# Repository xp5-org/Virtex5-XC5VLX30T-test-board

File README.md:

# 4 layer test-board for the XC5VLX30T-1FF665I-ND
schematic & pcb designed in Kicad 8
>This is a work in progress, i will update again after completing the bga reball work and confirming if the chips respond to jtag
>- capcaitor footprints not finalized (may need more depending on what testing reveals)
<br><br>

This project's goal is to fan out as many I/O pins as possible on the Virtex-5 665 BGA , 1mm pitch footprint, using a standard PCB service without any special work. This means:
- 0.3 drill size vias
- 0.15mm track spacing & track width
- 0.2mm copper-to-hole clearance
- 4 layers, 1oz
- NO microvia, blind via, buried via
- NO via-in-pad

With these constraints, I was able to pull 215 I/O pins on a standard 4-layer board.  
Warning: This design is on the extreme edge of "not following the manufacturers PCB design recommendations" with regards to the signal and power delivery
I'm not certain if this will work for any practical design (VGA, Ethernet, DDR-SDRAM). However it should be acceptable for hobby work and experimenting.
I initially planned to interface this Virtex-5 FPGA with some 3.3v cmos buffers and logic gates, high-speed wasn't a concern.
If the scrap-recovered chips i have respond & work, this design could be easily converted to a 6-layer to improve power plane & signal
<br><br>

# pcb ordering & build
For this 4-layer version, i had [PCBWay](https://www.pcbway.com/) build it and i put together a youtube video of what it looks like
- Current pcbway board - https://www.youtube.com/watch?v=_ErQVJeHTFE , here I am showing some close up photos reviewing what was built and received. In this video i can confirm what pcbway's capabilities are on standard pcb service, specifically in this board design there is some critical areas around hole drill precision & plating for the vias. the precision by pcbway will allow to use 0.15mm copper clearance in this design and can see in this video link.
- PCBWay by default offered 1oz copper on inner & outer layers, which gave more current carrying capability for VCCINT and VCCO
- order sheet for PCBWay - https://github.com/xp5-org/Virtex5-XC5VLX30T-test-board/blob/main/pcbway_4layer_order.png , this is using default options for 4-layer with the exception of trace width & spacing has been specified to 5mil

<br><br>

# Current Status
- this is the basic idea of what i'm working with. a Xilinx programmer is $30+ and a raspi with [XC3SPROG](https://xc3sprog.sourceforge.net/hardware.php) is $5
- the raspi will have to live on this device and use the jtag header to program the virtex5 on each use or powerup.
- There is a lot of I/O, but there's nothing else. no ram, no EPROM, no flash.

<br><br>

Power:  The virtex5 here needs 1.0V, 2.5V, and 3.3V
- I'm starting off with the MP2307 buck converter, its an inexpensive (and discontinued) chip found in the mini360 modules
- SMD version : https://github.com/xp5-org/Virtex5-XC5VLX30T-test-board/tree/main/XC5VLX30T_testboard/buck_converter_mp2307
- Through-hole version: https://github.com/xp5-org/Virtex5-XC5VLX30T-test-board/tree/main/XC5VLX30T_testboard/mp2307_tht

<br><br>

Next steps for testing:
- build the MP2307 buck converters
- reball the virtex5's using 0.6mm lead balls
 
<br><br><br><br>
# kicad screenshots of each layer
<br><br>

JTAG pins on the rear, clock and capacitors on the bottom GND plane side
headers for buck converters at the top of the board

Top Layer:

2nd Layer:

3rd Layer:

4th Layer:

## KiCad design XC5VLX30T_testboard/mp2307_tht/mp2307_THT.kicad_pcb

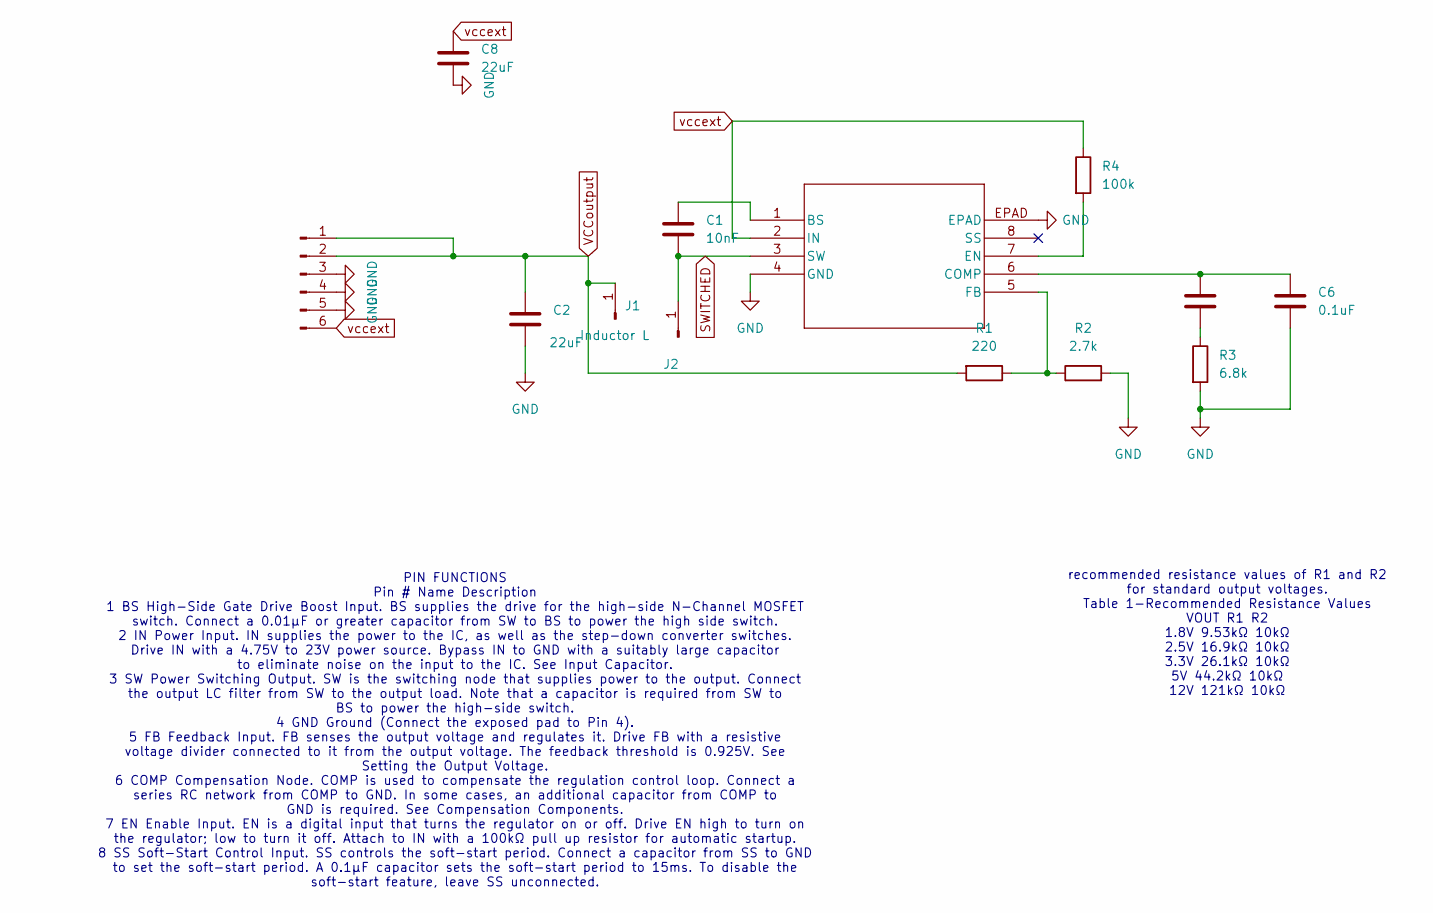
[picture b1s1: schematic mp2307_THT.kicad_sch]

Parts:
C1: 10nF; C_Disc_D3.0mm_W1.6mm_P2.50mm
C2, C8: 22uF; C_Disc_D3.0mm_W1.6mm_P2.50mm
C3: 3.9nF; C_Disc_D3.0mm_W1.6mm_P2.50mm
C6: 0.1uF; C_Disc_D3.0mm_W1.6mm_P2.50mm
J1: Inductor L; PinHeader_1x01_P2.54mm_Vertical
J2: Inductor_R; PinHeader_1x01_P2.54mm_Vertical
J4: Conn_01x06_Pin; virtex5_buck
R1: 220; R_Axial_DIN0204_L3.6mm_D1.6mm_P1.90mm_Vertical
R2: 2.7k; R_Axial_DIN0204_L3.6mm_D1.6mm_P1.90mm_Vertical
R3: 6.8k; R_Axial_DIN0204_L3.6mm_D1.6mm_P1.90mm_Vertical
R4: 100k; R_Axial_DIN0204_L3.6mm_D1.6mm_P1.90mm_Vertical
U1: MP2307DN-LF-Z; IC8_MP2307_MNP

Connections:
GND: C2.2, C6.2, C8.2, J4.3, J4.4, J4.5, R2.2, R3.2, U1.4 (GND), U1.EPAD
unnamed: C3.2, R3.1
unnamed: C1.1, U1.1 (BS)
unnamed: C3.1, C6.1, U1.6 (COMP)
unnamed: R4.2, U1.7 (EN)
unnamed: R1.1, R2.1, U1.5 (FB)
SWITCHED: C1.2, J2.1, U1.3 (SW)
VCCoutput: C2.1, J1.1, J4.1, J4.2, R1.2
vccext: C8.1, J4.6, R4.1, U1.2 (IN)

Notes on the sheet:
recommended resistance values of R1 and R2 for standard output voltages. Table 1-Recommended Resistance Values VOUT R1 R2 1.8V 9.53kΩ 10kΩ 2.5V 16.9kΩ 10kΩ 3.3V 26.1kΩ 10kΩ 5V 44.2kΩ 10kΩ 12V 121kΩ 10kΩ
PIN FUNCTIONS Pin # Name Description 1 BS High-Side Gate Drive Boost Input. BS supplies the drive for the high-side N-Channel MOSFET switch. Connect a 0.01μF or greater capacitor from SW to BS to power the high side switch. 2 IN Power Input. IN supplies the power to the IC, as well as the step-down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

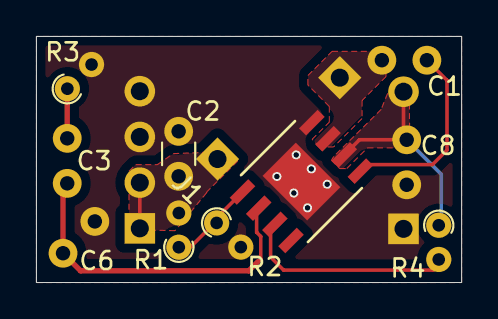
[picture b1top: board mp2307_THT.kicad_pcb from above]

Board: 2 copper layers, 23.6 x 13.7 mm, 13 parts (0 on the bottom side), 9 nets.

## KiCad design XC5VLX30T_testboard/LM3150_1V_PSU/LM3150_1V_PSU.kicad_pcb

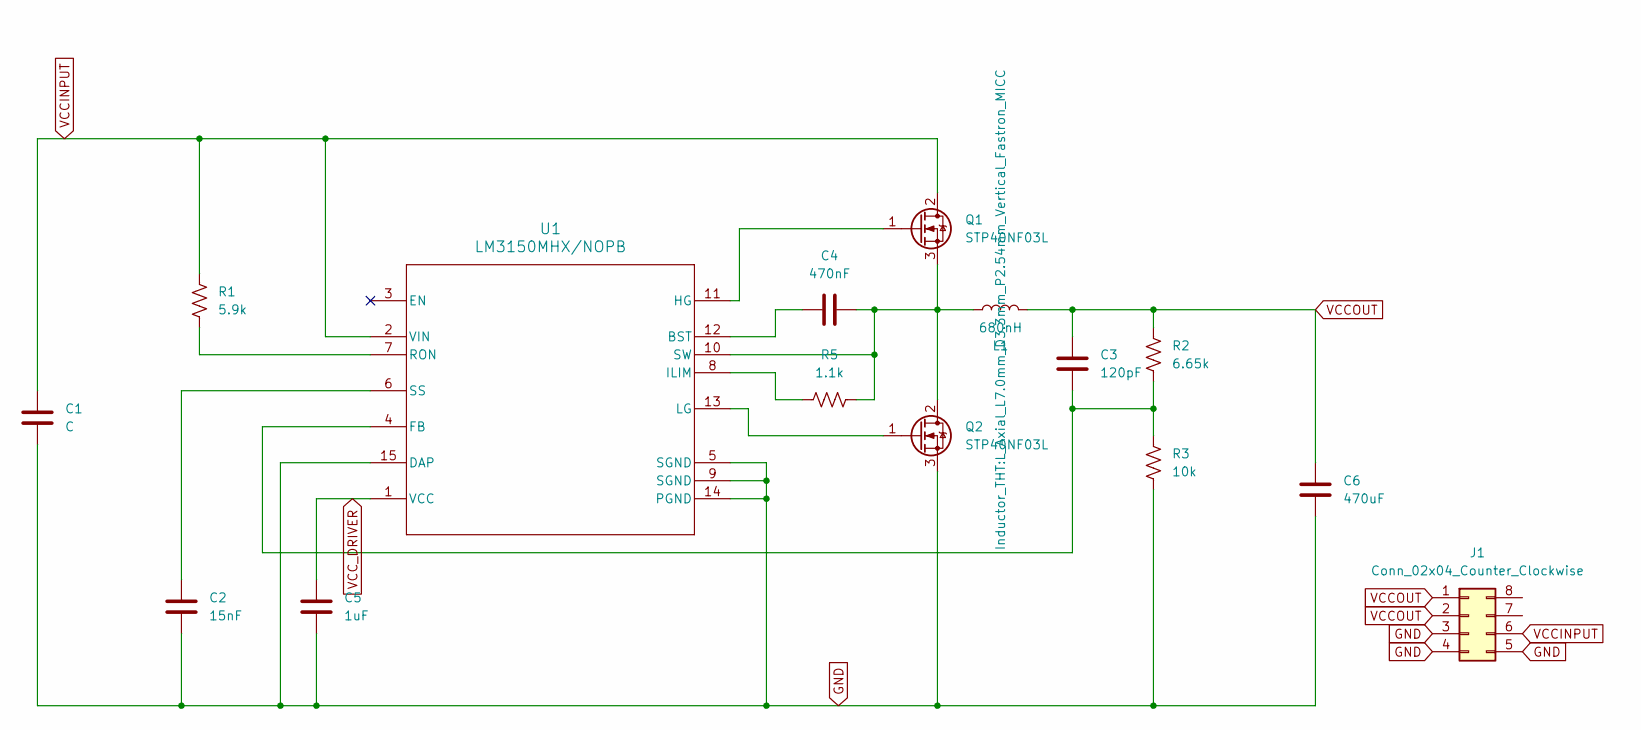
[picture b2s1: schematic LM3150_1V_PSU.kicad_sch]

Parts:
C1: C; C_Disc_D3.0mm_W2.0mm_P2.50mm
C2: 15nF; C_Disc_D3.0mm_W1.6mm_P2.50mm
C3: 120pF; C_Disc_D3.0mm_W1.6mm_P2.50mm
C4: 470nF; C_Disc_D3.0mm_W1.6mm_P2.50mm
C5: 1uF; C_Disc_D3.0mm_W1.6mm_P2.50mm
C6: 470uF; C_Disc_D3.0mm_W1.6mm_P2.50mm
J1: Conn_02x04_Counter_Clockwise; virtex5_buck
L1: 680nH; L_Axial_L7.0mm_D3.3mm_P2.54mm_Vertical_Fastron_MICC
Q1, Q2: STP40NF03L; TO-220-3_Vertical
R1: 5.9k; R_Axial_DIN0204_L3.6mm_D1.6mm_P5.08mm_Horizontal
R2: 6.65k; R_Axial_DIN0204_L3.6mm_D1.6mm_P5.08mm_Horizontal
R3: 10k; R_Axial_DIN0204_L3.6mm_D1.6mm_P5.08mm_Horizontal
R5: 1.1k; R_Axial_DIN0204_L3.6mm_D1.6mm_P5.08mm_Horizontal
U1: LM3150MHX/NOPB; HTSSOP-14-1EP_4.4x5mm_P0.65mm_EP3.4x5mm_Mask3x3.1mm_Thermal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

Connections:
GND: C1.2, C2.2, C5.2, C6.2, J1.3, J1.4, J1.5, Q2.3 (S), R3.2, U1.5 (SGND), U1.9 (SGND), U1.14 (PGND), U1.15 (DAP)
unnamed: Q1.1 (G), U1.11 (HG)
unnamed: C4.1, L1.2, Q1.3 (S), Q2.2 (D), R5.1, U1.10 (SW)
unnamed: Q2.1 (G), U1.13 (LG)
unnamed: C4.2, U1.12 (BST)
unnamed: C3.2, R2.2, R3.1, U1.4 (FB)
unnamed: R5.2, U1.8 (ILIM)
unnamed: R1.2, U1.7 (RON)
unnamed: C2.1, U1.6 (SS)
VCCINPUT: C1.1, J1.6, Q1.2 (D), R1.1, U1.2 (VIN)
VCCOUT: C3.1, C6.1, J1.1, J1.2, L1.1, R2.1
VCC_DRIVER: C5.1, U1.1 (VCC)

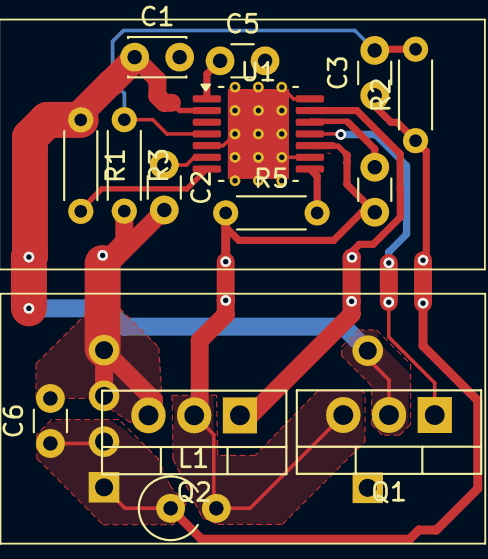
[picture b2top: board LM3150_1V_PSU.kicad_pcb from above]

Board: 2 copper layers, 15 parts (0 on the bottom side), 12 nets.

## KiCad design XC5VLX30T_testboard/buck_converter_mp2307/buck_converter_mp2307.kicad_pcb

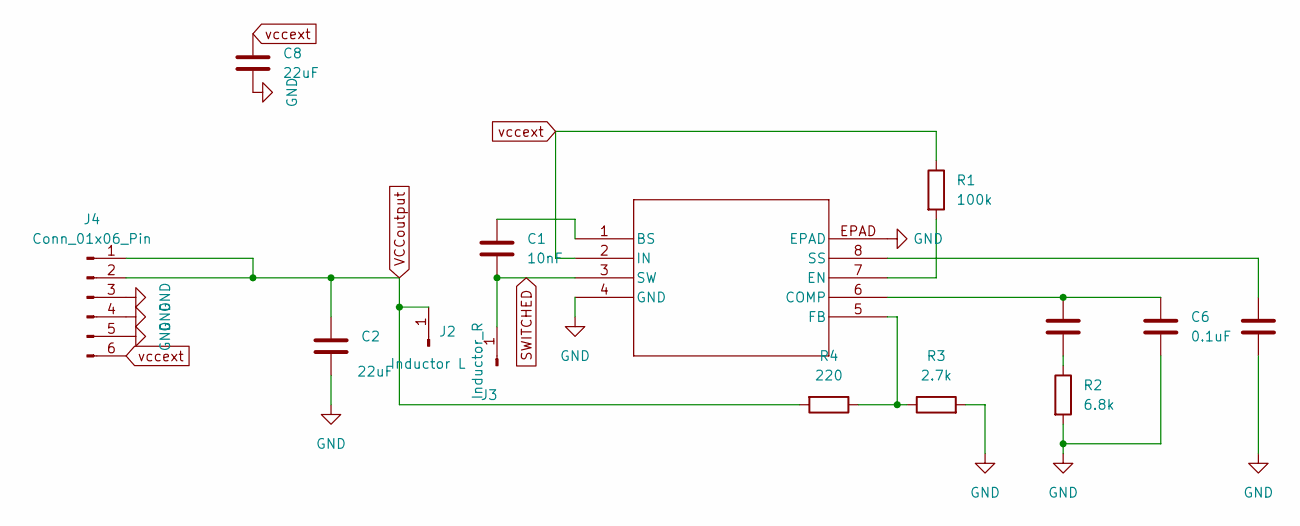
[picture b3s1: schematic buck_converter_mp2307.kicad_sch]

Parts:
C1: 10nF; C_0603_1608Metric
C2, C8: 22uF; C_1206_3216Metric
C3: 3.9nF; C_0603_1608Metric
C4, C6: 0.1uF; C_0603_1608Metric
J2: Inductor L; PinHeader_1x01_P2.54mm_Vertical
J3: Inductor_R; PinHeader_1x01_P2.54mm_Vertical
J4: Conn_01x06_Pin; virtex5_buck
R1: 100k; R_0603_1608Metric
R2: 6.8k; R_0603_1608Metric
R3: 2.7k; R_0603_1608Metric
R4: 220; R_0603_1608Metric
U1: MP2307DN-LF-Z; IC8_MP2307_MNP

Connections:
GND: C2.2, C4.2, C6.2, C8.2, J4.3, J4.4, J4.5, R2.2, R3.2, U1.4 (GND), U1.EPAD
unnamed: C3.2, R2.1
unnamed: C1.1, U1.1 (BS)
unnamed: C3.1, C6.1, U1.6 (COMP)
unnamed: R1.2, U1.7 (EN)
unnamed: R3.1, R4.1, U1.5 (FB)
unnamed: C4.1, U1.8 (SS)
SWITCHED: C1.2, J3.1, U1.3 (SW)
VCCoutput: C2.1, J2.1, J4.1, J4.2, R4.2
vccext: C8.1, J4.6, R1.1, U1.2 (IN)

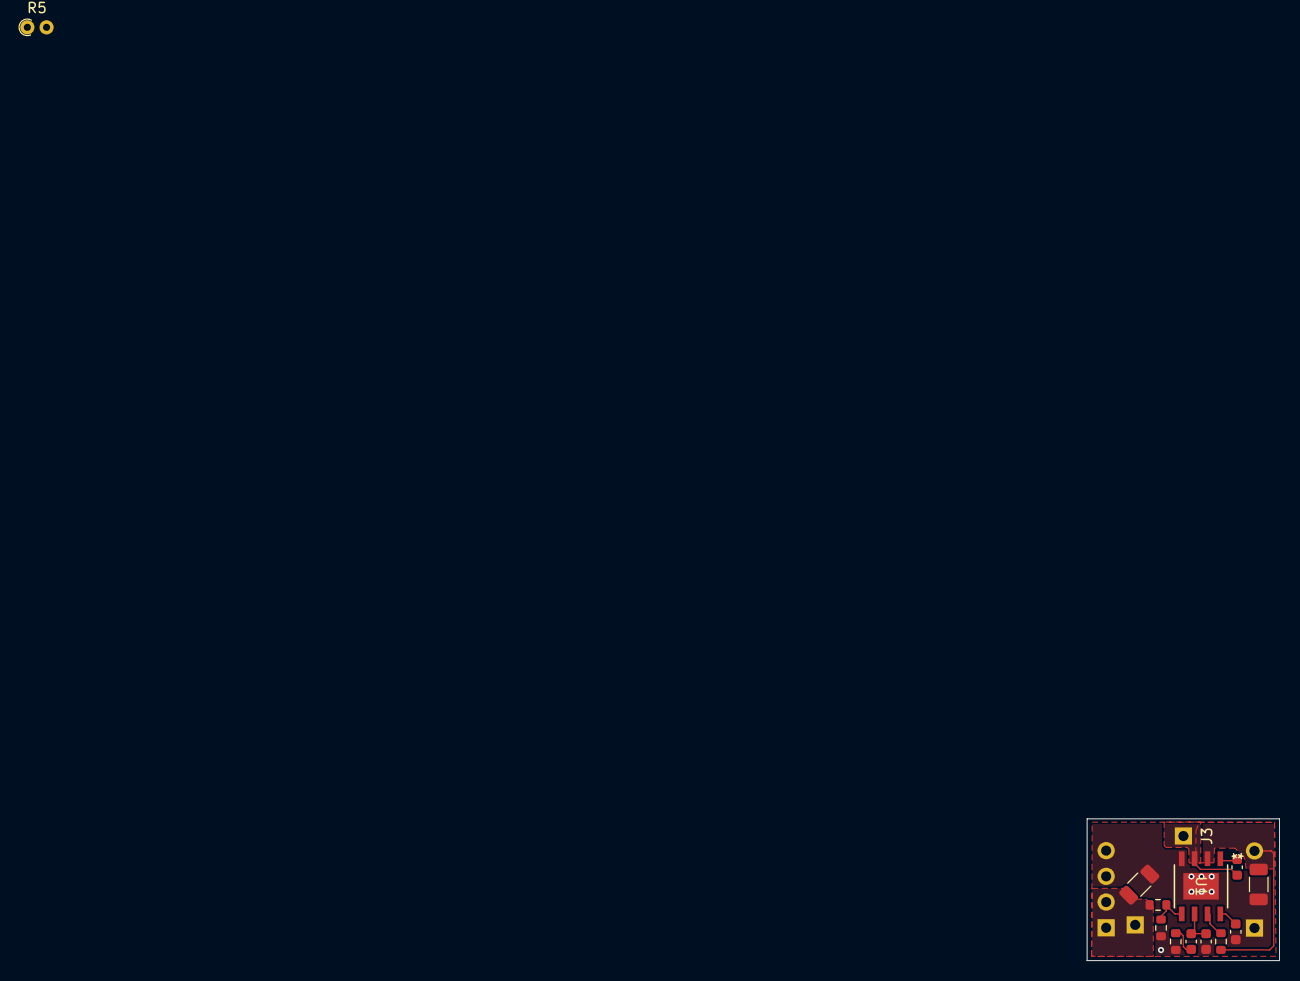
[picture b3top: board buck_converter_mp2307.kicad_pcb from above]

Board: 2 copper layers, 19.0 x 14.0 mm, 15 parts (0 on the bottom side), 10 nets.

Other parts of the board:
R5: R; R_Axial_DIN0204_L3.6mm_D1.6mm_P1.90mm_Vertical

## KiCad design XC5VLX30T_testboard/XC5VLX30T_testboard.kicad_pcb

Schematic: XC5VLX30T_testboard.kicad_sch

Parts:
C1, C6: 470uF; CP_EIA-3216-10_Kemet-I
C2, C3, C4, C5, C7, C8, C9, C10, C11, C12, C13, C14, C15, C16, C17: 470uF; CP_EIA-3216-12_Kemet-S
J1, J2, J3, J4, J5, J6, J7, J8: Conn_01x35_Pin; PinHeader_1x35_P1.27mm_Vertical
J9: Conn_02x03; PinHeader_2x03_P2.54mm_Vertical
J10: pi_zero_footprint_placeholder; 23x58pizero
J11: Conn_01x02_Pin; PinSocket_1x02_P2.54mm_Vertical
J15, J16, J17: Conn_01x06_Pin; virtex5_buck
R1, R2, R3: R; R_0201_0603Metric
TP1, TP2, TP3, TP4, TP5, TP6, TP7, TP8, TP9: TestPoint; Pin_D0.7mm_L6.5mm_W1.8mm_FlatFork
U1: XC5VLX30T-1FFG665C; digikey665-FBGA_XIL
X1: SG-5032CCN; Crystal_SMD_3225-4Pin_3.2x2.5mm_HandSoldering

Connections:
CLK: U1.AC17 (IO_L8P_CC_GC_4), X1.3 (OUT)
CLK_AUX1: TP5.1, U1.D16 (IO_L1P_CC_GC_3)
GND: C1.2, C2.2, C3.2, C4.2, C5.2, C6.2, C7.2, C8.2, C9.2, C10.2, C11.2, C12.2, C13.2, C14.2, C15.2, C16.2, C17.2, J1.1, J1.7, J1.14, J1.21, J1.28, J1.35, J2.1, J2.7, J2.14, J2.21, J2.28, J2.35, J3.1, J3.7, J3.14, J3.26, J3.27, J3.28, J3.29, J4.1, J4.2, J4.3, J4.4, J4.5, J4.6, J4.7, J4.14, J4.21, J4.28, J4.35, J5.1, J5.7, J5.14, J5.21, J5.28, J5.35, J6.1, J6.7, J6.14, J6.21, J6.28, J6.35, J7.1, J7.7, J7.14, J7.21, J7.28, J7.35, J8.1, J8.7, J8.14, J8.21, J8.28, J8.35, J9.2, J11.1, J15.3, J15.4, J15.5, J16.3, J16.4, J16.5, J17.3, J17.4, J17.5, R1.2, U1.A2 (GND), U1.A6 (GND), U1.A11 (GND), U1.A16 (GND), U1.A21 (GND), U1.A26 (GND), U1.AA1 (MGTRXP0_118), U1.AA3 (MGTAVTTRX_118), U1.AA4 (GND), U1.AA11 (GND), U1.AA21 (GND), U1.AA26 (GND), U1.AB1 (MGTRXN0_118), U1.AB2 (GND), U1.AB8 (GND), U1.AB18 (GND), U1.AC1 (MGTRXN1_118), U1.AC2 (GND), U1.AC5 (GND), U1.AC15 (GND), U1.AC25 (GND), U1.AD1 (MGTRXP1_118), U1.AD3 (MGTAVCCPLL_118), U1.AD12 (GND), U1.AD22 (GND), U1.AE3 (MGTAVTTTX_118), U1.AE4 (GND), U1.AE9 (GND), U1.AE19 (GND), U1.AF2 (GND), U1.AF6 (GND), U1.AF11 (GND), U1.AF16 (GND), U1.AF21 (GND), U1.AF26 (GND), U1.B3 (MGTAVTTTX_116), U1.B8 (GND), U1.B18 (GND), U1.C1 (MGTRXP0_116), U1.C3 (MGTAVTTRX_116), U1.C4 (GND), U1.C5 (GND), U1.C15 (GND), U1.C20 (GND), U1.C25 (GND), U1.D1 (MGTRXN0_116), U1.D2 (GND), U1.D12 (GND), U1.D22 (GND), U1.E1 (MGTRXN1_116), U1.E2 (GND), U1.E9 (GND), U1.E19 (GND), U1.F1 (MGTRXP1_116), U1.F2 (MGTTXN1_116), U1.F3 (MGTAVCCPLL_116), U1.F4 (GND), U1.F6 (GND), U1.F16 (GND), U1.F26 (GND), U1.G3 (MGTAVTTTX_116), U1.G13 (GND), U1.G23 (GND), U1.H3 (MGTAVTTTX_112), U1.H10 (GND), U1.H14 (GND), U1.H16 (GND), U1.H20 (GND), U1.J1 (MGTRXP0_112), U1.J3 (MGTAVTTRX_112), U1.J4 (GND), U1.J7 (GND), U1.J13 (GND), U1.J15 (GND), U1.J17 (GND), U1.K1 (MGTRXN0_112), U1.K2 (GND), U1.K10 (GND), U1.K12 (GND), U1.K14 (GND), U1.K16 (GND), U1.K18 (GND), U1.K24 (GND), U1.L1 (MGTRXN1_112), U1.L2 (GND), U1.L9 (GND), U1.L11 (GND), U1.L13 (GND), U1.L15 (GND), U1.L17 (GND), U1.L19 (GND), U1.L21 (GND), U1.L26 (GND), U1.M1 (MGTRXP1_112), U1.M3 (MGTAVCCPLL_112), U1.M4 (GND), U1.M8 (GND), U1.M10 (GND), U1.M12 (GND), U1.M16 (GND), U1.M18 (GND), U1.N3 (MGTAVTTTX_112), U1.N5 (GND), U1.N9 (GND), U1.N11 (GND), U1.N13 (GND), U1.N17 (GND), U1.N19 (GND), U1.N25 (GND), U1.P3 (MGTAVTTTX_114), U1.P4 (MGTRREF_112), U1.P10 (GND), U1.P12 (GND), U1.P16 (GND), U1.P18 (GND), U1.P22 (GND), U1.R1 (MGTRXP0_114), U1.R3 (MGTAVTTRX_114), U1.R4 (GND), U1.R9 (GND), U1.R11 (GND), U1.R13 (GND), U1.R17 (GND), U1.R19 (GND), U1.T1 (MGTRXN0_114), U1.T2 (GND), U1.T6 (GND), U1.T10 (GND), U1.T12 (GND), U1.T14 (GND), U1.T16 (GND), U1.T18 (GND), U1.T21 (GND), U1.T26 (GND), U1.U1 (MGTRXN1_114), U1.U2 (GND), U1.U9 (GND), U1.U11 (GND), U1.U13 (GND), U1.U15 (GND), U1.U17 (GND), U1.U19 (GND), U1.U23 (GND), U1.V1 (MGTRXP1_114), U1.V3 (MGTAVCCPLL_114), U1.V4 (GND), U1.V5 (GND), U1.V10 (GND), U1.V14 (GND), U1.V16 (GND), U1.V18 (GND), U1.V20 (GND), U1.W3 (MGTAVTTTX_114), U1.W7 (GND), U1.W12 (GND), U1.W15 (GND), U1.W17 (GND), U1.W19 (GND), U1.Y3 (MGTAVTTTX_118), U1.Y9 (GND), U1.Y14 (GND), U1.Y24 (GND), X1.2 (GND)
IO_L0N_11: J5.12, U1.E25 (IO_L0N_11)
IO_L0N_12: J2.3, U1.Y5 (IO_L0N_12)
IO_L0N_15: J4.9, U1.C14 (IO_L0N_15)
IO_L0N_17: J8.11, U1.AD26 (IO_L0N_17)
IO_L0N_18: J7.33, U1.AE12 (IO_L0N_18)
IO_L0N_SM8N_13: J6.16, U1.R26 (IO_L0N_SM8N_13)
IO_L0P_11: J5.16, U1.E26 (IO_L0P_11)
IO_L0P_12: J2.4, U1.Y6 (IO_L0P_12)
IO_L0P_15: J4.8, U1.C13 (IO_L0P_15)
IO_L0P_17: J8.10, U1.AC26 (IO_L0P_17)
IO_L0P_18: J7.32, U1.AF12 (IO_L0P_18)
IO_L0P_SM8P_13: J6.11, U1.P26 (IO_L0P_SM8P_13)
IO_L1N_11: J5.24, U1.G26 (IO_L1N_11)
IO_L1N_15: J3.24, U1.A13 (IO_L1N_15)
IO_L1N_17: J8.17, U1.AD24 (IO_L1N_17)
IO_L1N_SM7N_13: J6.18, U1.R25 (IO_L1N_SM7N_13)
IO_L1P_11: J5.17, U1.F25 (IO_L1P_11)
IO_L1P_12: J1.11, U1.G6 (IO_L1P_12)
IO_L1P_15: J4.11, U1.B14 (IO_L1P_15)
IO_L1P_17: J8.13, U1.AD25 (IO_L1P_17)
IO_L1P_SM7P_13: J6.13, U1.P25 (IO_L1P_SM7P_13)
IO_L2N_11: J5.23, U1.G25 (IO_L2N_11)
IO_L2N_12: J1.32, U1.W4 (IO_L2N_12)
IO_L2N_15: J4.12, U1.A15 (IO_L2N_15)
IO_L2N_17: J8.12, U1.AE26 (IO_L2N_17)
IO_L2N_18: J7.27, U1.AD11 (IO_L2N_18)
IO_L2P_11: J5.25, U1.H26 (IO_L2P_11)
IO_L2P_12: J1.33, U1.Y4 (IO_L2P_12)
IO_L2P_15: J4.10, U1.A14 (IO_L2P_15)
IO_L2P_17: J8.16, U1.AE25 (IO_L2P_17)
IO_L2P_18: J7.34, U1.AE11 (IO_L2P_18)
IO_L2P_SM6P_13: J6.15, U1.P24 (IO_L2P_SM6P_13)
IO_L3N_11: J5.19, U1.G24 (IO_L3N_11)
IO_L3N_12: J1.8, U1.F5 (IO_L3N_12)
IO_L3N_17: J8.18, U1.AF24 (IO_L3N_17)
IO_L3N_SM5N_13: J6.19, U1.R22 (IO_L3N_SM5N_13)
IO_L3P_11: J5.20, U1.F24 (IO_L3P_11)
IO_L3P_12: J1.10, U1.G5 (IO_L3P_12)
IO_L3P_15: J4.13, U1.B15 (IO_L3P_15)
IO_L3P_17: J8.15, U1.AF25 (IO_L3P_17)
IO_L3P_GC_D9_4: J7.31, U1.AC11 (IO_L3P_GC_D9_4)
IO_L3P_SM5P_13: J6.17, U1.R23 (IO_L3P_SM5P_13)
IO_L4N_GC_VREF_4: J8.32, U1.AC19 (IO_L4N_GC_VREF_4)
IO_L4N_VREF_12: J1.34, U1.W6 (IO_L4N_VREF_12)
IO_L4N_VREF_13: J6.29, U1.V26 (IO_L4N_VREF_13)
IO_L4N_VREF_16: J3.17, U1.A8 (IO_L4N_VREF_16)
IO_L4N_VREF_17: J8.19, U1.AE23 (IO_L4N_VREF_17)
IO_L4N_VREF_18: J2.32, U1.AE10 (IO_L4N_VREF_18)
IO_L4P_11: J5.13, U1.E23 (IO_L4P_11)
IO_L4P_12: J2.2, U1.W5 (IO_L4P_12)
IO_L4P_13: J6.24, U1.U26 (IO_L4P_13)
IO_L4P_15: J4.15, U1.B16 (IO_L4P_15)
IO_L4P_16: J3.16, U1.A9 (IO_L4P_16)
IO_L4P_17: J8.23, U1.AF23 (IO_L4P_17)
IO_L4P_18: J2.30, U1.AD10 (IO_L4P_18)
IO_L5N_15: J4.16, U1.A17 (IO_L5N_15)
IO_L5N_17: J8.24, U1.AD23 (IO_L5N_17)
IO_L5N_GC_4: J7.25, U1.AC13 (IO_L5N_GC_4)
IO_L5N_SM4N_13: J6.22, U1.T25 (IO_L5N_SM4N_13)
IO_L5P_12: J1.9, U1.G4 (IO_L5P_12)
IO_L5P_15: J4.17, U1.B17 (IO_L5P_15)
IO_L5P_17: J8.25, U1.AE22 (IO_L5P_17)
IO_L5P_GC_4: J7.29, U1.AC12 (IO_L5P_GC_4)
IO_L5P_SM4P_13: J6.26, U1.U25 (IO_L5P_SM4P_13)
IO_L6N_15: J4.20, U1.A19 (IO_L6N_15)
IO_L6N_16: J3.12, U1.C8 (IO_L6N_16)
IO_L6N_17: J8.20, U1.AC23 (IO_L6N_17)
IO_L6N_18: J2.34, U1.AF10 (IO_L6N_18)
IO_L6N_D6_2: J7.23, U1.AA14 (IO_L6N_D6_2)
IO_L6P_11: J5.18, U1.G22 (IO_L6P_11)
IO_L6P_12: J1.31, U1.V6 (IO_L6P_12)
IO_L6P_15: J4.18, U1.A18 (IO_L6P_15)
IO_L6P_16: J3.15, U1.B9 (IO_L6P_16)
IO_L6P_17: J8.9, U1.AC24 (IO_L6P_17)
IO_L6P_18: J2.33, U1.AF9 (IO_L6P_18)
IO_L6P_GC_4: J8.34, U1.AC18 (IO_L6P_GC_4)
IO_L6P_SM3P_13: J6.23, U1.T24 (IO_L6P_SM3P_13)
IO_L7N_11: J5.22, U1.J23 (IO_L7N_11)
IO_L7N_12: J1.12, U1.J6 (IO_L7N_12)
IO_L7N_15: J4.19, U1.C18 (IO_L7N_15)
IO_L7N_16: J3.2, U1.D6 (IO_L7N_16)
IO_L7N_GC_VRP: J7.19, U1.AC14 (IO_L7N_GC_VRP_4)
IO_L7N_SM2N_13: J6.27, U1.V24 (IO_L7N_SM2N_13)
IO_L7P_12: J1.13, U1.J5 (IO_L7P_12)
IO_L7P_15: J4.22, U1.B19 (IO_L7P_15)
IO_L7P_16: J1.4, U1.E6 (IO_L7P_16)
IO_L7P_17: J8.26, U1.AC22 (IO_L7P_17)
IO_L7P_GC_VRN_4: J7.22, U1.AB14 (IO_L7P_GC_VRN_4)
IO_L8N_CC_15: J4.25, U1.B20 (IO_L8N_CC_15)
IO_L8N_CC_16: J3.13, U1.D8 (IO_L8N_CC_16)
IO_L8N_CC_17: J8.27, U1.AE21 (IO_L8N_CC_17)
IO_L8N_CC_18: J2.25, U1.AF8 (IO_L8N_CC_18)
IO_L8N_CC_SM1N_13: J6.30, U1.W25 (IO_L8N_CC_SM1N_13)
IO_L8P_CC_15: J4.23, U1.A20 (IO_L8P_CC_15)
IO_L8P_CC_16: J3.18, U1.C9 (IO_L8P_CC_16)
IO_L8P_CC_17: J8.29, U1.AF22 (IO_L8P_CC_17)
IO_L8P_CC_18: J2.22, U1.AF7 (IO_L8P_CC_18)
IO_L8P_CC_GC_4: J7.9, U1.AC16 (IO_L9N_CC_GC_4)
IO_L8P_CC_SM1P_13: J6.32, U1.W26 (IO_L8P_CC_SM1P_13)
IO_L9N_CC_11: J5.31, U1.K23 (IO_L9N_CC_11)
IO_L9N_CC_12: J1.17, U1.L5 (IO_L9N_CC_12)
IO_L9N_CC_16: J3.4, U1.C6 (IO_L9N_CC_16)
IO_L9N_CC_17: J8.33, U1.AE20 (IO_L9N_CC_17)
IO_L9N_CC_18: J2.6, U1.AB5 (IO_L9N_CC_18)
IO_L9P_CC_11: J5.33, U1.K22 (IO_L9P_CC_11)
IO_L9P_CC_12: J1.16, U1.K5 (IO_L9P_CC_12)
IO_L9P_CC_16: J3.11, U1.C7 (IO_L9P_CC_16)
IO_L9P_CC_17: J7.3, U1.AF20 (IO_L9P_CC_17)
IO_L9P_CC_18: J2.5, U1.AA5 (IO_L9P_CC_18)
IO_L9P_CC_SM0P_13: J6.31, U1.W24 (IO_L9P_CC_SM0P_13)
IO_L10N_CC_16: J3.9, U1.B7 (IO_L10N_CC_16)
IO_L10N_CC_17: J8.31, U1.AD20 (IO_L10N_CC_17)
IO_L10P_CC_12: J1.15, U1.K6 (IO_L10P_CC_12)
IO_L10P_CC_15: J4.24, U1.D21 (IO_L10P_CC_15)
IO_L10P_CC_16: J3.10, U1.A7 (IO_L10P_CC_16)
IO_L10P_CC_17: J7.2, U1.AD19 (IO_L10P_CC_17)
IO_L10P_CC_18: J2.8, U1.AB6 (IO_L10P_CC_18)
IO_L11N_CC_12: J1.30, U1.U5 (IO_L11N_CC_12)
IO_L11N_CC_13: J6.34, U1.W23 (IO_L11N_CC_13)
IO_L11N_CC_15: J4.31, U1.C21 (IO_L11N_CC_15)
IO_L11N_CC_17: J8.22, U1.AD21 (IO_L11N_CC_17)
IO_L11N_CC_18: J2.20, U1.AE7 (IO_L11N_CC_18)
IO_L11P_CC_12: J1.27, U1.U6 (IO_L11P_CC_12)
IO_L11P_CC_15: J4.26, U1.B21 (IO_L11P_CC_15)
IO_L11P_CC_16: J3.25, U1.D9 (IO_L11P_CC_16)
IO_L11P_CC_17: J8.30, U1.AC21 (IO_L11P_CC_17)
IO_L11P_CC_18: J2.26, U1.AE8 (IO_L11P_CC_18)
IO_L12N_VRP_11: J5.26, U1.J24 (IO_L12N_VRP_11)
IO_L12N_VRP_13: J8.2, U1.Y25 (IO_L12N_VRP_13)
IO_L12N_VRP_15: J4.33, U1.C22 (IO_L12N_VRP_15)
IO_L12N_VRP_16: J3.6, U1.A5 (IO_L12N_VRP_16)
IO_L12N_VRP_17: J7.12, U1.AF18 (IO_L12N_VRP_17)
IO_L12N_VRP_18: J2.9, U1.AD5 (IO_L12N_VRP_18)
IO_L12P_VRN_13: J6.33, U1.Y26 (IO_L12P_VRN_13)
IO_L12P_VRN_15: J5.10, U1.D23 (IO_L12P_VRN_15)
IO_L12P_VRN_16: J3.8, U1.B6 (IO_L12P_VRN_16)
IO_L12P_VRN_17: J7.6, U1.AF19 (IO_L12P_VRN_17)
IO_L12P_VRN_18: J2.23, U1.AC6 (IO_L12P_VRN_18)
IO_L13N_11: J5.29, U1.J26 (IO_L13N_11)
IO_L13N_12: J1.25, U1.R5 (IO_L13N_12)
IO_L13N_13: J8.5, U1.AB26 (IO_L13N_13)
IO_L13N_15: J4.27, U1.A22 (IO_L13N_15)
IO_L13N_16: J3.19, U1.A10 (IO_L13N_16)
IO_L13N_17: J7.4, U1.AD18 (IO_L13N_17)
IO_L13N_18: J2.18, U1.AF5 (IO_L13N_18)
IO_L13P_11: J5.27, U1.J25 (IO_L13P_11)
IO_L13P_12: J1.29, U1.T5 (IO_L13P_12)
IO_L13P_13: J8.3, U1.AA25 (IO_L13P_13)
IO_L13P_15: J4.29, U1.B22 (IO_L13P_15)
IO_L13P_16: J3.20, U1.B10 (IO_L13P_16)
IO_L13P_17: J7.5, U1.AE18 (IO_L13P_17)
IO_L13P_18: J2.15, U1.AE6 (IO_L13P_18)
IO_L14N_VREF_11: J6.2, U1.L25 (IO_L14N_VREF_11)
IO_L14N_VREF_13: J8.8, U1.AA24 (IO_L14N_VREF_13)
IO_L14N_VREF_15: J4.32, U1.A24 (IO_L14N_VREF_15)
IO_L14N_VREF_16: J1.3, U1.A3 (IO_L14N_VREF_16)
IO_L14N_VREF_17: J7.13, U1.AF17 (IO_L14N_VREF_17)
IO_L14N_VREF_18: J2.11, U1.AD4 (IO_L14N_VREF_18)
IO_L14P_11: J5.30, U1.K26 (IO_L14P_11)
IO_L14P_13: J8.4, U1.AB25 (IO_L14P_13)
IO_L14P_15: J4.30, U1.A23 (IO_L14P_15)
IO_L14P_16: J3.3, U1.A4 (IO_L14P_16)
IO_L14P_17: J7.10, U1.AE17 (IO_L14P_17)
IO_L14P_18: J2.10, U1.AE5 (IO_L14P_18)
IO_L15N_12: J1.26, U1.T7 (IO_L15N_12)
IO_L15N_15: J5.6, U1.C23 (IO_L15N_15)
IO_L15N_16: J3.22, U1.A12 (IO_L15N_16)
IO_L15N_17: J7.8, U1.AD16 (IO_L15N_17)
IO_L15N_18: J2.12, U1.AF3 (IO_L15N_18)
IO_L15N_SM13N_11: J5.32, U1.K25 (IO_L15N_SM13N_11)
IO_L15P_12: J1.23, U1.R6 (IO_L15P_12)
IO_L15P_13: J8.6, U1.AB24 (IO_L15P_13)
IO_L15P_15: J5.2, U1.B24 (IO_L15P_15)
IO_L15P_16: J3.21, U1.B11 (IO_L15P_16)
IO_L15P_17: J7.11, U1.AE16 (IO_L15P_17)
IO_L15P_18: J2.17, U1.AF4 (IO_L15P_18)
IO_L15P_CC_SM13P_11: J5.34, U1.L24 (IO_L15P_SM13P_11)
IO_L16N_12: J1.19, U1.N6 (IO_L16N_12)
IO_L16N_15: J5.4, U1.C24 (IO_L16N_15)
IO_L16N_16: J3.5, U1.B5 (IO_L16N_16)
IO_L16N_17: J7.18, U1.AE15 (IO_L16N_17)
IO_L16N_18: J2.24, U1.AC7 (IO_L16N_18)
IO_L16N_SM12N_11: J6.6, U1.M26 (IO_L16N_SM12N_11)
IO_L16P_12: J1.20, U1.P6 (IO_L16P_12)
IO_L16P_15: J5.11, U1.D24 (IO_L16P_15)
IO_L16P_16: J1.2, U1.B4 (IO_L16P_16)
IO_L16P_17: J7.17, U1.AD15 (IO_L16P_17)
IO_L16P_18: J2.13, U1.AD6 (IO_L16P_18)
IO_L16P_SM12P_11: J6.9, U1.N26 (IO_L16P_SM12P_11)
IO_L17N_12: J1.22, U1.N7 (IO_L17N_12)
IO_L17N_13: J6.20, U1.U22 (IO_L17N_13)
IO_L17N_15: J4.34, U1.A25 (IO_L17N_15)
IO_L17N_17: J7.15, U1.AF14 (IO_L17N_17)
IO_L17N_18: J2.19, U1.AD8 (IO_L17N_18)
IO_L17N_SM11N_11: J6.3, U1.M24 (IO_L17N_SM11N_11)
IO_L17P_12: J1.18, U1.M6 (IO_L17P_12)
IO_L17P_15: J5.3, U1.B25 (IO_L17P_15)
IO_L17P_16: J3.23, U1.B12 (IO_L17P_16)
IO_L17P_17: J7.16, U1.AF15 (IO_L17P_17)
IO_L17P_18: J2.29, U1.AC8 (IO_L17P_18)
IO_L17P_SM11P_11: J6.4, U1.M25 (IO_L17P_SM11P_11)
IO_L18N_13: J6.25, U1.V22 (IO_L18N_13)
IO_L18N_15: J5.8, U1.C26 (IO_L18N_15)
IO_L18N_16: J1.6, U1.E5 (IO_L18N_16)
IO_L18N_17: J7.24, U1.AE13 (IO_L18N_17)
IO_L18N_18: J2.31, U1.AC9 (IO_L18N_18)
IO_L18N_SM10N_11: J6.10, U1.N23 (IO_L18N_SM10N_11)
IO_L18P_15: J5.5, U1.B26 (IO_L18P_15)
IO_L18P_16: J1.5, U1.D5 (IO_L18P_16)
IO_L18P_17: J7.30, U1.AF13 (IO_L18P_17)
IO_L18P_18: J2.27, U1.AD9 (IO_L18P_18)
IO_L18P_SM10P_11: J6.5, U1.N24 (IO_L18P_SM10P_11)
IO_L19N_12: J1.24, U1.R7 (IO_L19N_12)
IO_L19N_15: J5.9, U1.D25 (IO_L19N_15)
IO_L19N_17: J7.20, U1.AD14 (IO_L19N_17)
IO_L19N_SM9N_11: J6.8, U1.M22 (IO_L19N_SM9N_11)
IO_L19P_15: J5.15, U1.D26 (IO_L19P_15)
IO_L19P_17: J7.26, U1.AD13 (IO_L19P_17)
IO_L19P_SM9P_11: J6.12, U1.N22 (IO_L19P_SM9P_11)
M0_MODESELECT: R3.1, U1.T20 (M0_0)
M1_MODESELECT: R1.1, U1.W20 (M1_0)
M2_MODESELECT: R2.1, U1.U20 (M2_0)
TCK: TP2.1, U1.V11 (TCK_0)
TCK_PAD: J9.5, TP8.1
TDI: TP3.1, U1.V13 (TDI_0)
TDI_PAD: J9.4, TP7.1
TDO: TP1.1, U1.V12 (TDO_0)
TDO_PAD: J9.6, TP9.1
TMS: TP4.1, U1.W13 (TMS_0)
TMS_PAD: J9.3, TP6.1
VCCO: C4.1, C8.1, C9.1, C10.1, C11.1, C12.1, C13.1, J9.1, J17.1, J17.2, R2.2, R3.2, U1.AA6 (VCCO_18), U1.AA16 (VCCO_2), U1.AB13 (VCCO_4), U1.AB23 (VCCO_17), U1.AC10 (VCCO_18), U1.AC20 (VCCO_17), U1.AD7 (VCCO_18), U1.AD17 (VCCO_2), U1.AE14 (VCCO_4), U1.AE24 (VCCO_17), U1.B13 (VCCO_1), U1.B23 (VCCO_15), U1.C10 (VCCO_16), U1.D7 (VCCO_16), U1.D17 (VCCO_3), U1.E14 (VCCO_1), U1.E24 (VCCO_15), U1.F11 (VCCO_0), U1.F21 (VCCO_15), U1.G8 (VCCO_16), U1.G18 (VCCO_3), U1.H5 (VCCO_12), U1.H25 (VCCO_11), U1.J12 (VCCO_0), U1.J22 (VCCO_11), U1.L6 (VCCO_12), U1.M23 (VCCO_11), U1.P7 (VCCO_12), U1.R24 (VCCO_13), U1.V25 (VCCO_13), U1.W22 (VCCO_13), X1.1 (OE), X1.4 (Vcc)
VccAUX: C5.1, C7.1, C15.1, J15.1, J15.2, U1.K9 (VCCAUX), U1.M9 (VCCAUX), U1.M19 (VCCAUX), U1.N20 (VCCAUX), U1.P9 (VCCAUX), U1.P19 (VCCAUX), U1.T9 (VCCAUX), U1.T19 (VCCAUX), U1.U8 (VCCAUX), U1.V19 (VCCAUX), U1.W10 (VCCAUX), U1.Y19 (VCCAUX)
VccINT: C1.1, C2.1, C3.1, C6.1, J16.1, J16.2, U1.AC3 (MGTAVCC_118), U1.AC4 (MGTAVCC_118), U1.E3 (MGTAVCC_116), U1.E4 (MGTAVCC_116), U1.H15 (VCCINT), U1.H17 (VCCINT), U1.J14 (VCCINT), U1.J16 (VCCINT), U1.J18 (VCCINT), U1.K13 (VCCINT), U1.K15 (VCCINT), U1.K17 (VCCINT), U1.K19 (VCCINT), U1.L3 (MGTAVCC_112), U1.L4 (MGTAVCC_112), U1.L10 (VCCINT), U1.L12 (VCCINT), U1.L14 (VCCINT), U1.L16 (VCCINT), U1.L18 (VCCINT), U1.M11 (VCCINT), U1.M13 (VCCINT), U1.M17 (VCCINT), U1.N10 (VCCINT), U1.N12 (VCCINT), U1.N16 (VCCINT), U1.N18 (VCCINT), U1.P11 (VCCINT), U1.P13 (VCCINT), U1.P17 (VCCINT), U1.R10 (VCCINT), U1.R12 (VCCINT), U1.R16 (VCCINT), U1.R18 (VCCINT), U1.T11 (VCCINT), U1.T13 (VCCINT), U1.T15 (VCCINT), U1.T17 (VCCINT), U1.U3 (MGTAVCC_114), U1.U4 (MGTAVCC_114), U1.U10 (VCCINT), U1.U14 (VCCINT), U1.U16 (VCCINT), U1.U18 (VCCINT), U1.V15 (VCCINT), U1.V17 (VCCINT), U1.W18 (VCCINT)
vccext: C14.1, C16.1, C17.1, J3.30, J3.31, J3.32, J3.33, J3.34, J3.35, J11.2, J15.6, J16.6, J17.6

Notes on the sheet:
power converters
vccext capacitors
vccaux capacitors
VCCO capacitors
jtag pins bottom side
FPGA
active crystal osc

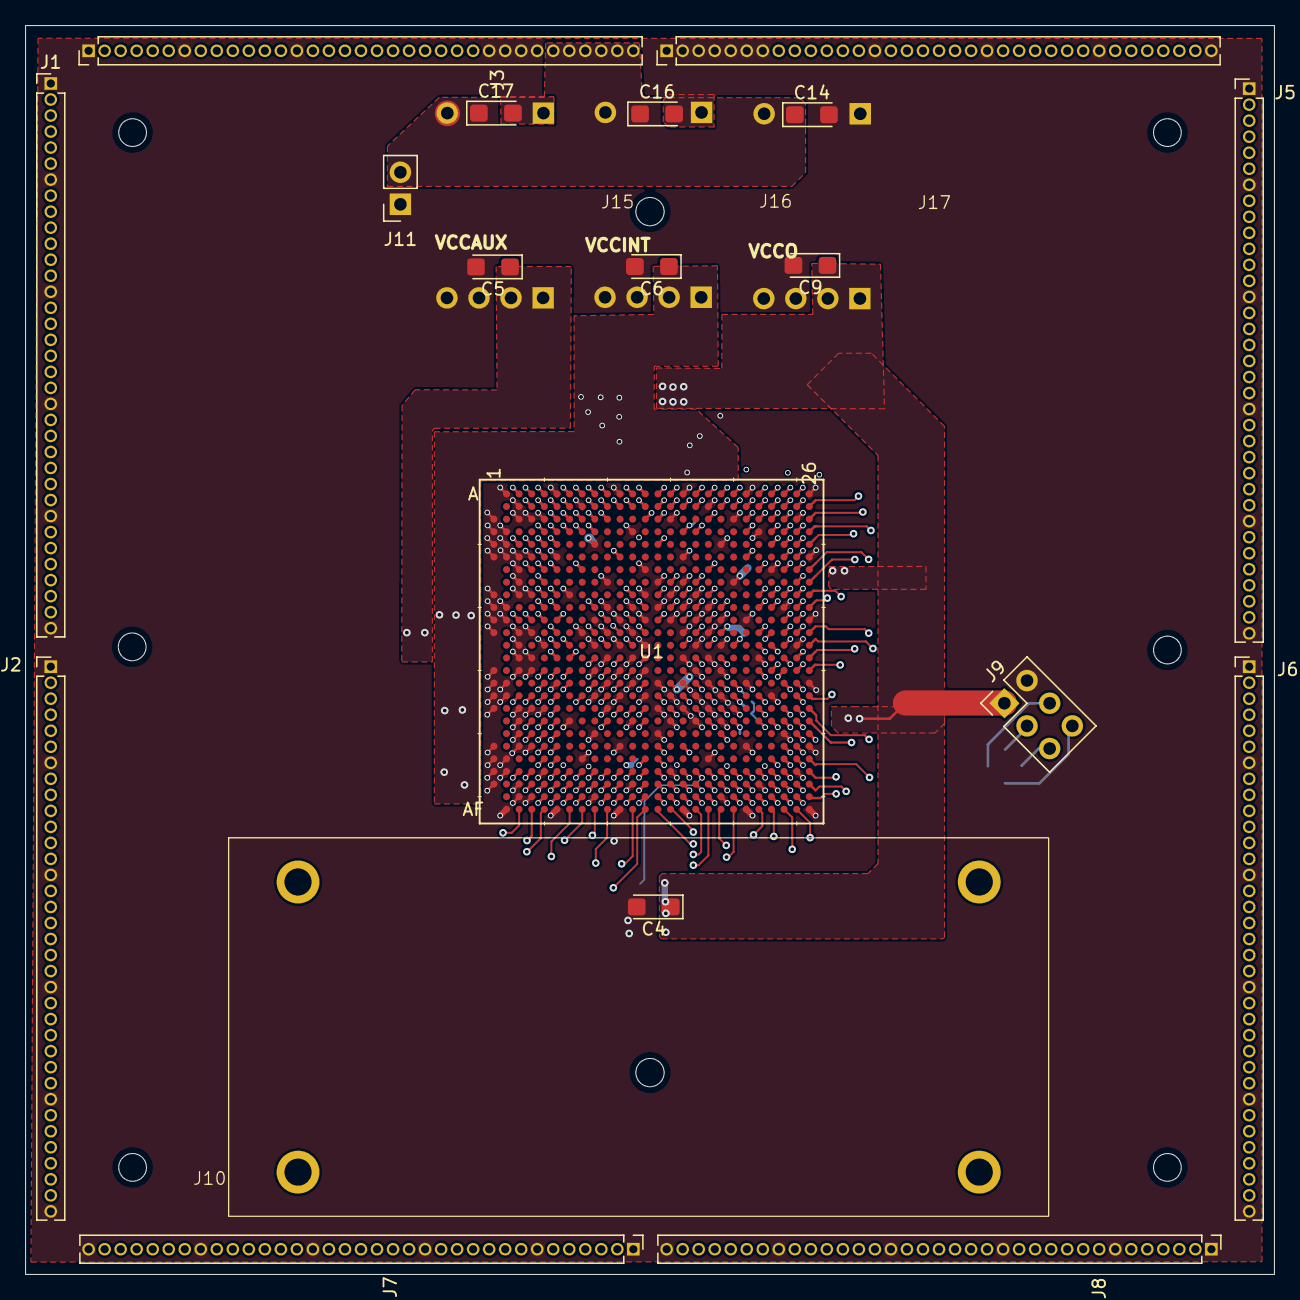
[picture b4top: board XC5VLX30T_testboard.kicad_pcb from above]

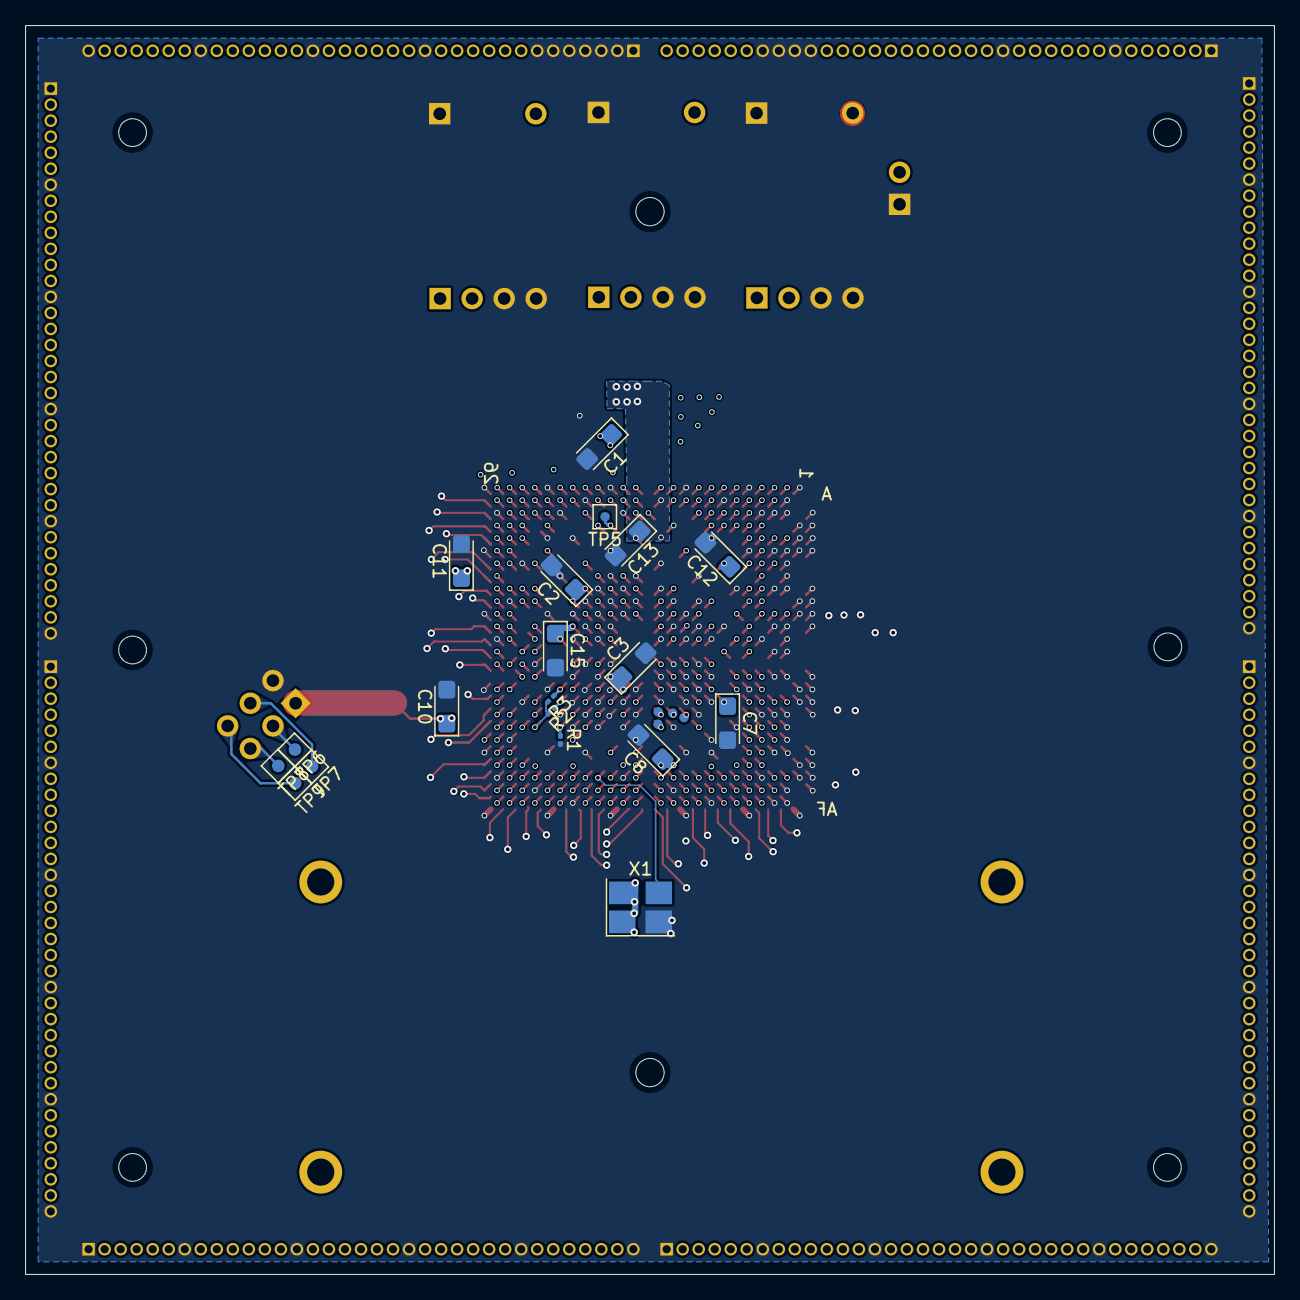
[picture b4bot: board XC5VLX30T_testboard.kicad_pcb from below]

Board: 4 copper layers, 99.0 x 99.0 mm, 45 parts (23 on the bottom side), 237 nets.

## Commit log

2024-06-14 added library + symbol from ultralibrarian
2024-08-04 fixed missing gnd and vcc nets
2024-08-14 more work
2024-08-15 vcco layout
2024-08-18 setup mtttx ports to use case 9
2024-08-24 routing
    routed 240 pins on 4 layer
2024-08-31 plumbing
2024-09-02 via routing
2024-09-05 fixed missing pins
    MGTRXP/MGTRXN wasnt connected to GND
2024-09-08 more routing
2024-09-11 fixed DRC check errors
2024-09-12 routing
2024-09-12 convert all vias to through hole
2024-09-15 more i/o routing and labels
2024-09-20 more routing
    almost done routing to pins
2024-09-21 mostly finished routing
2024-09-28 through hole pads for buck converters
2024-09-28 more clicking
2024-09-29 mode select pins + pull down resistors
    "If the Virtex-5 device is configured via JTAG on power-up, it is advisable to tie the mode pins to the Boundary-Scan configuration mode settings: 101 (M2 = 1, M1 = 0,
    M0 = 1)."
2024-10-08 resize wires to .13mm
    resized wires to 0.13mm
    added top layer gnd plane, vccaux plane
2024-10-08 moved clock to P from N
2024-10-10 added jtag header and pi zero footprint
2024-10-11 gnd planes
2024-10-14 fixed misaligned header pins
    header pins were off by a few mm in every direction, tried to align them within 0.005mm
2024-10-18 removed 4 i/o for wider vccint
2024-10-18 reworking vias
2024-10-19 centered holes
2024-10-20 more vias work
2024-10-23 set holes to pad type
2024-10-25 reordered headers
2024-10-26 text labels
2024-10-26 added tht version of mp2307 board
2024-10-27 fixed text on back silkscreen
2024-10-29 fixed vias with no L1 connection
2024-10-29 replaced 3216 with 1310 capacitors
    didnt need such large capacitor footprints
2024-11-03 added kicad via check tool
    kicad needs external DRC tool to validate if all vias have a top layer component otherwise they cant be built as THT vias must be built as blind or buried
2024-11-06 lm3150 psu
    alternate psu using lm3150
2024-11-25 changed from MP pad to regular pad
2024-12-02 pcbway order example
    added build sheet for pcbway 4 layer
2024-12-02 move footprints to parent dir
2024-12-02 dot underscore cleanup
    remote garbage mac files
2024-12-02 Update README.md
    added summary for 1st pcb build review
2024-12-02 Update README.md
    clarified the capacitor footprints are still unverified, may need to add more depending on results
2024-12-13 update mp2307 tht resistor labels
    resistor labels on mp2307 tht board now match datasheet
